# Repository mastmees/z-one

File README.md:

# z-one
Z-One is a CP/M machine with SD card storage, 80x30 character VGA output, and PS/2 keyboard

See the project page at http://www.nomad.ee/micros/z-one/ for details.

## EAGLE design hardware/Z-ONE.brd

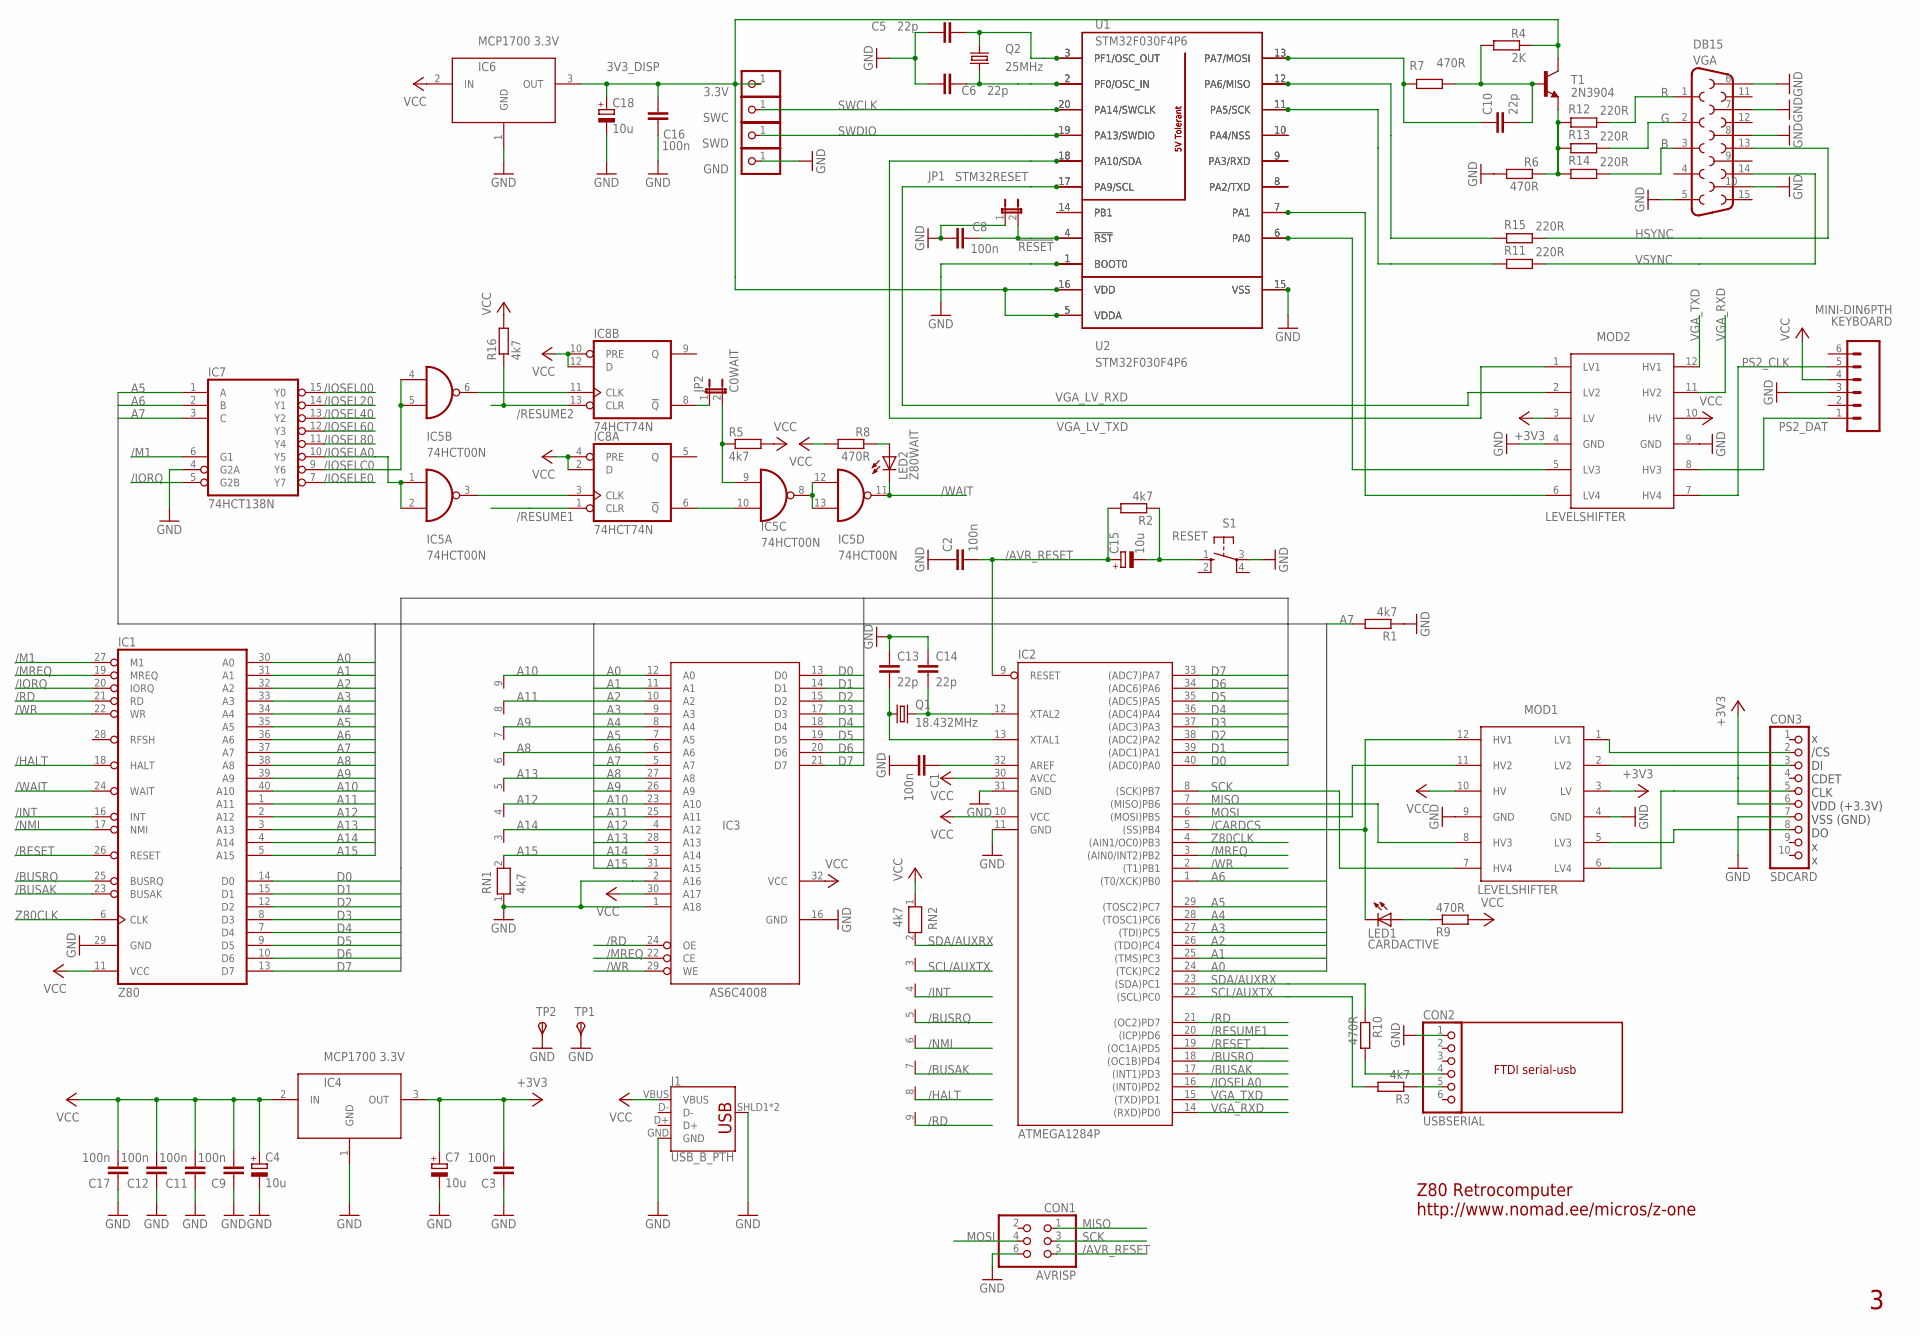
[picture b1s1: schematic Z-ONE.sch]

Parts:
3.3V: PINHD-1X1; 1X01
C1, C2, C3, C8, C9, C11, C12, C16, C17: 100n; C025-025X050; PARTNO 0.1UF, 0603
C4, C7, C15, C18: 10u; E2,5-5
C5, C6, C10: 22p; C025-025X050; PARTNO 22PF, 0603
C13, C14: 22p; C025-025X050; PARTNO 0.1UF, 0603
CON1: AVRISP; 2X03
CON2: USBSERIAL; 1X06
CON3: SDCARD; 1X10
GND: PINHD-1X1; 1X01
IC1: Z80; DIL40
IC2: ATMEGA1284P; DIL40
IC3: AS6C4008; DIP32
IC4, IC6: MCP1700 3.3V; TO-92
IC5: 74HCT00N; DIL14
IC7: 74HCT138N; DIL16
IC8: 74HCT74N; DIL14
J1: USB_B_PTH; USB-B-PTH
JP1: STM32RESET; 1X02
JP2: C0WAIT; 1X02
KEYBOARD: MINI-DIN6PTH; MINI-DIN6
LED1: CARDACTIVE; LED3MM
LED2: Z80WAIT; LED3MM
MOD1, MOD2: LEVELSHIFTER; LAVELSHIFTER_N
Q1: 18.432MHz; HC49/S
Q2: 25MHz; HC49/S
R1, R2, R3, R5, R16: 4k7; 0204/7
R4: 2K; 0204/7; PARTNO 2K, 0603
R6, R7, R8, R9: 470R; 0204/7; PARTNO 475R, 0603
R10: 470R; 0204/7
R11, R12, R13, R14, R15: 220R; 0204/7
RN1, RN2: 4k7; RN-9
S1: RESET; B3F-10XX
SWC: PINHD-1X1; 1X01
SWD: PINHD-1X1; 1X01
T1: 2N3904; TO92
TP1, TP2: GND; P1-13
U1: STM32F030F4P6; DIL20WIDE
U2: STM32F030F4P6; MISC-PROCESSOR_TSSOP20
VGA: DB15

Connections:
3V3_DISP: 3.3V.1, C16.1, C18.+, IC6.3 (OUT), R4.1, T1.1 (C), U1.5 (VDDA), U1.16 (VDD), U2.5 (VDDA), U2.16 (VDD)
25MHZ: C5.2, Q2.2, U1.3 (PF1/OSC_OUT), U2.3 (PF1/OSC_OUT)
!RESET: C8.1, JP1.2, U1.4 (!RST), U2.4 (!RST)
+3.3V: C3.2, C7.+, CON3.6, IC4.3 (OUT), MOD1.3 (LV), MOD2.3 (LV)
/AVR_RESET: C2.2, C15.+, CON1.5, IC2.9 (RESET), R2.2
/BUSAK: IC1.23 (BUSAK), IC2.17 ((INT1)PD3), RN2.7
/BUSRQ: IC1.25 (BUSRQ), IC2.18 ((OC1B)PD4), RN2.5
/CARDCS: IC2.5 ((SS)PB4), LED1.K (C), MOD1.12 (HV1)
/HALT: IC1.18 (HALT), RN2.8
/INT: IC1.16 (INT), RN2.4
/IORQ: IC1.20 (IORQ), IC7.5 (G2B)
/IOSEL00: IC7.15 (Y0)
/IOSEL20: IC7.14 (Y1)
/IOSEL40: IC7.13 (Y2)
/IOSEL60: IC7.12 (Y3)
/IOSEL80: IC7.11 (Y4)
/IOSELA0: IC2.16 ((INT0)PD2), IC5.1 (I0), IC5.2 (I1), IC7.10 (Y5)
/IOSELC0: IC5.4 (I0), IC5.5 (I1), IC7.9 (Y6)
/IOSELE0: IC7.7 (Y7)
/M1: IC1.27 (M1), IC7.6 (G1)
/MREQ: IC1.19 (MREQ), IC2.3 ((AIN0/INT2)PB2), IC3.22 (CE)
/NMI: IC1.17 (NMI), RN2.6
/RD: IC1.21 (RD), IC2.21 ((OC2)PD7), IC3.24 (OE), RN2.9
/RESET: IC1.26 (RESET), IC2.19 ((OC1A)PD5)
/RESUME1: IC2.20 ((ICP)PD6), IC8.1 (CLR)
/RESUME2: IC8.13 (CLR), R16.1
/WAIT: IC1.24 (WAIT), IC5.11 (O), LED2.K (C)
/WR: IC1.22 (WR), IC2.2 ((T1)PB1), IC3.29 (WE)
A0: IC1.30 (A0), IC2.24 ((TCK)PC2), IC3.12 (A0)
A1: IC1.31 (A1), IC2.25 ((TMS)PC3), IC3.11 (A1)
A2: IC1.32 (A2), IC2.26 ((TDO)PC4), IC3.10 (A2)
A3: IC1.33 (A3), IC2.27 ((TDI)PC5), IC3.9 (A3)
A4: IC1.34 (A4), IC2.28 ((TOSC1)PC6), IC3.8 (A4)
A5: IC1.35 (A5), IC2.29 ((TOSC2)PC7), IC3.7 (A5), IC7.1 (A)
A6: IC1.36 (A6), IC2.1 ((T0/XCK)PB0), IC3.6 (A6), IC7.2 (B)
A7: IC1.37 (A7), IC3.5 (A7), IC7.3 (C), R1.2
A8: IC1.38 (A8), IC3.27 (A8), RN1.6
A9: IC1.39 (A9), IC3.26 (A9), RN1.7
A10: IC1.40 (A10), IC3.23 (A10), RN1.9
A11: IC1.1 (A11), IC3.25 (A11), RN1.8
A12: IC1.2 (A12), IC3.4 (A12), RN1.4
A13: IC1.3 (A13), IC3.28 (A13), RN1.5
A14: IC1.4 (A14), IC3.3 (A14), RN1.3
A15: IC1.5 (A15), IC3.31 (A15), RN1.2
B: R14.1, VGA.3
D0: IC1.14 (D0), IC2.40 ((ADC0)PA0), IC3.13 (D0)
D1: IC1.15 (D1), IC2.39 ((ADC1)PA1), IC3.14 (D1)
D2: IC1.12 (D2), IC2.38 ((ADC2)PA2), IC3.15 (D2)
D3: IC1.8 (D3), IC2.37 ((ADC3)PA3), IC3.17 (D3)
D4: IC1.7 (D4), IC2.36 ((ADC4)PA4), IC3.18 (D4)
D5: IC1.9 (D5), IC2.35 ((ADC5)PA5), IC3.19 (D5)
D6: IC1.10 (D6), IC2.34 ((ADC6)PA6), IC3.20 (D6)
D7: IC1.13 (D7), IC2.33 ((ADC7)PA7), IC3.21 (D7)
G: R13.1, VGA.2
GND: C1.2, C2.1, C3.1, C4.-, C5.1, C6.1, C7.-, C8.2, C9.1, C11.1, C12.1, C13.1, C14.1, C16.2, C17.1, C18.-, CON1.6, CON2.1, CON3.7, GND.1, IC1.29 (GND), IC2.11 (GND), IC2.31 (GND), IC3.1 (A18), IC3.2 (A16), IC3.16 (GND), IC4.1 (GND), IC5.7 (GND), IC6.1 (GND), IC7.4 (G2A), IC7.8 (GND), IC8.7 (GND), J1.GND, J1.SHLD1 (SHIELD), J1.SHLD2 (SHIELD), JP1.1, KEYBOARD.3, MOD1.4 (GND), MOD1.9 (GND), MOD2.4 (GND), MOD2.9 (GND), R1.1, R6.2, RN1.1, S1.3, TP1.TP, TP2.TP, U1.1 (BOOT0), U1.15 (VSS), U2.1 (BOOT0), U2.15 (VSS), VGA.5, VGA.6, VGA.7, VGA.8, VGA.10
HSYNC: R15.1, VGA.13
MISO: CON1.1, IC2.7 ((MISO)PB6), MOD1.8 (HV3)
MOSI: CON1.4, IC2.6 ((MOSI)PB5), MOD1.11 (HV2)
unnamed: C6.2, Q2.1, U1.2 (PF0/OSC_IN), U2.2 (PF0/OSC_IN)
unnamed: R15.2, U1.12 (PA6/MISO), U2.12 (PA6/MISO)
unnamed: IC5.3 (O), IC8.3 (CLK)
unnamed: R6.1, R12.2, R13.2, R14.2, T1.3 (E)
unnamed: C14.2, IC2.12 (XTAL2), Q1.2
unnamed: C1.1, IC2.32 (AREF)
unnamed: R11.2, U1.11 (PA5/SCK), U2.11 (PA5/SCK)
unnamed: MOD2.6 (LV4), U1.7 (PA1), U2.7 (PA1)
unnamed: MOD2.5 (LV3), U1.6 (PA0), U2.6 (PA0)
unnamed: C10.2, R4.2, R7.1, T1.2 (B)
unnamed: C10.1, R7.2, U1.13 (PA7/MOSI), U2.13 (PA7/MOSI)
unnamed: U1.8 (PA2/TXD), U2.8 (PA2/TXD)
unnamed: CON2.5, R3.1
unnamed: CON3.3, MOD1.2 (LV2)
unnamed: IC5.9 (I0), JP2.2, R5.1
unnamed: CON3.8, MOD1.5 (LV3)
unnamed: CON3.5, MOD1.6 (LV4)
unnamed: IC5.6 (O), IC8.11 (CLK)
unnamed: C13.2, IC2.13 (XTAL1), Q1.1
unnamed: U1.9 (PA3/RXD), U2.9 (PA3/RXD)
unnamed: IC8.8 (!Q), JP2.1
unnamed: U1.10 (PA4/NSS), U2.10 (PA4/NSS)
unnamed: CON2.4, R10.2
unnamed: U1.14 (PB1), U2.14 (PB1)
unnamed: IC5.10 (I1), IC8.6 (!Q)
unnamed: C15.-, R2.1, S1.1 (S)
unnamed: CON3.2, MOD1.1 (LV1)
unnamed: IC5.8 (O), IC5.12 (I0), IC5.13 (I1)
unnamed: LED2.A, R8.1
unnamed: LED1.A, R9.1
PS2_CLK: KEYBOARD.5, MOD2.7 (HV4)
PS2_DAT: KEYBOARD.1, MOD2.8 (HV3)
R: R12.1, VGA.1
SCK: CON1.3, IC2.8 ((SCK)PB7), MOD1.7 (HV4)
SCL/AUXTX: IC2.22 ((SCL)PC0), R3.2, RN2.3
SDA/AUXRX: IC2.23 ((SDA)PC1), R10.1, RN2.2
SWCLK: SWC.1, U1.20 (PA14/SWCLK), U2.20 (PA14/SWCLK)
SWDIO: SWD.1, U1.19 (PA13/SWDIO), U2.19 (PA13/SWDIO)
VCC: C4.+, C9.2, C11.2, C12.2, C17.2, IC1.11 (VCC), IC2.10 (VCC), IC2.30 (AVCC), IC3.30 (A17), IC3.32 (VCC), IC4.2 (IN), IC5.14 (VCC), IC6.2 (IN), IC7.16 (VCC), IC8.2 (D), IC8.4 (PRE), IC8.10 (PRE), IC8.12 (D), IC8.14 (VCC), J1.VBUS, KEYBOARD.4, MOD1.10 (HV), MOD2.10 (HV), R5.2, R8.2, R9.2, R16.2, RN2.1
VGA_LV_RXD: MOD2.2 (LV2), U1.17 (PA9/SCL), U2.17 (PA9/SCL)
VGA_LV_TXD: MOD2.1 (LV1), U1.18 (PA10/SDA), U2.18 (PA10/SDA)
VGA_RXD: IC2.14 ((RXD)PD0), MOD2.11 (HV2)
VGA_TXD: IC2.15 ((TXD)PD1), MOD2.12 (HV1)
VSYNC: R11.1, VGA.14
Z80CLK: IC1.6 (CLK), IC2.4 ((AIN1/OC0)PB3)

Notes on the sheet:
FTDI serial-usb
x /CS DI CDET CLK VDD (+3.3V) VSS (GND) DO x x
Z80 Retrocomputer http://www.nomad.ee/micros/z-one

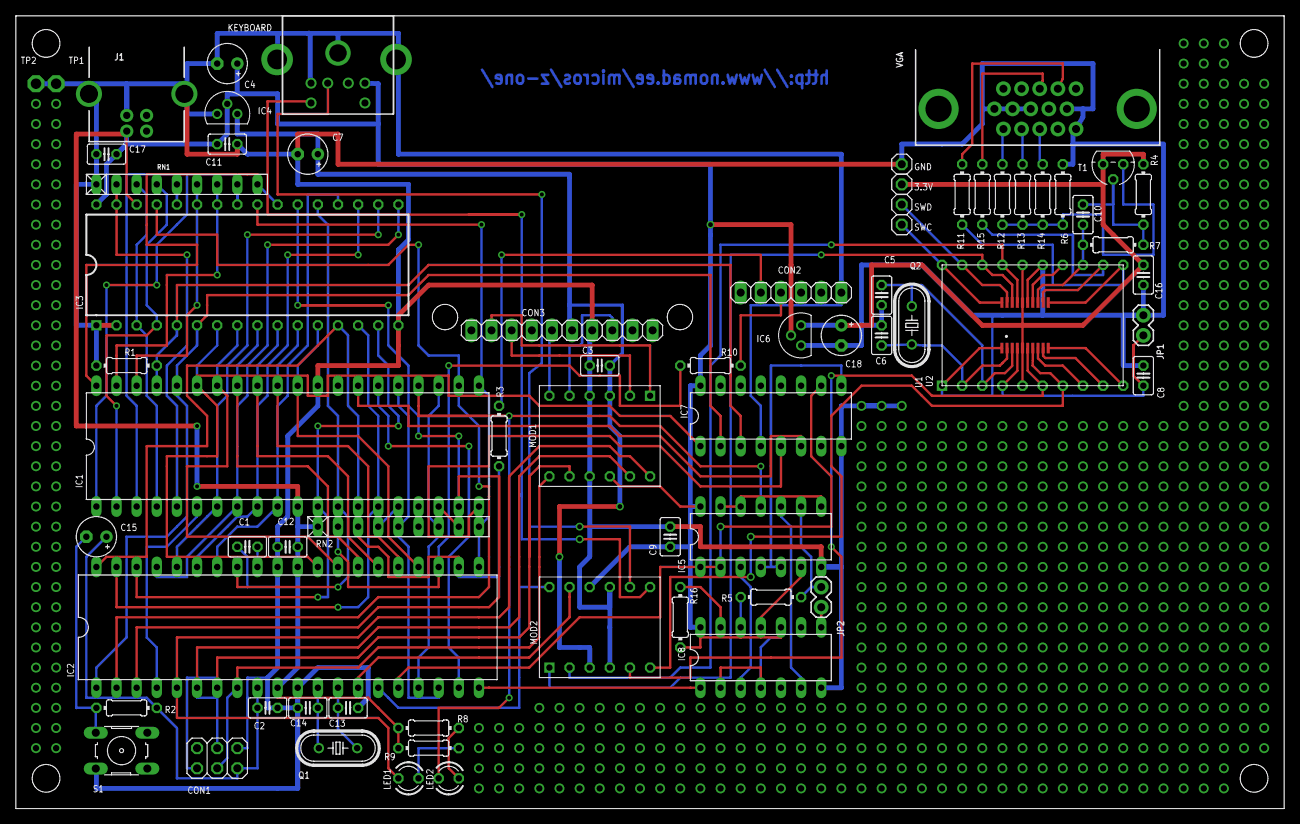
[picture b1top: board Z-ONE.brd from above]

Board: 2 copper layers, 160.0 x 100.0 mm, 68 parts (0 on the bottom side), 97 nets.

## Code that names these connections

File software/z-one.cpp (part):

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  PORTD|=0x20;   // z80 reset high
  PORTD&=~(0x40);
  PORTD|=0x40;   // ensure z80 is not in wait state
  while (PIND&0x08) // wait for BUSAK to go low
    ;
  // z80 bus is now floating, enable adr,data,and control outputs
  // to prepare for writing bootloader to ram
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  PORTC=0xff;
  DDRC=0xfc; // a0..a5
  PORTB|=7;
  DDRB|=7; // a6, /wr, /mreq
}

void release_bus()
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I/O configuration
-----------------
I/O pin                               direction    DDR  PORT
PA0 D0                                input        0    1
PA1 D1                                input        0    1
PA2 D2                                input        0    1
PA3 D3                                input        0    1
PA4 D4                                input        0    1
PA5 D5                                input        0    1
PA6 D6                                input        0    1
PA7 D7                                input        0    1

PB0 A6                                input        0    1
PB1 /WR                               input        0    1
PB2 /MREQ                             input        0    1
PB3 Z80CLK                            input        0    1
PB4 /SS                               input        0    1
PB5 MOSI                              input        0    1
PB6 MISO                              input        0    1
PB7 SCK                               input        0    1

PC0 SCL / sw uart tx                  input        0    0
PC1 SDA / sw uart rx                  input        0    0
PC2 A0                                input        0    1
PC3 A1                                input        0    1
PC4 A2                                input        0    1
PC5 A3                                input        0    1
PC6 A4                                input        0    1
PC7 A5                                input        0    1

PD0 RxD                               input        0    1
PD1 TxD                               output       1    1
PD2 /IOSELE0                          input        0    0
PD3 /BUSAK                            input        0    1
PD4 /BUSRQ                            input        0    1
PD5 /RESET                            output       1    0
PD6 /RESUME                           output       1    1
PD7 /RD                               input        0    1
*/
int main(void)
{
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
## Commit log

2018-08-02 Publishing to github and web
2018-08-02 adding prebuilt binaries
2018-08-02 provided link to project page

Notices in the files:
software/z-one.cpp:
The MIT License (MIT)
Copyright (c) 2018 Madis Kaal <mast@nomad.ee>
parts and their libraries:
SparkFun-Retired: Licensing: Creative Commons ShareAlike 4.0 International - https://creativecommons.org/licenses/by-sa/4.0
